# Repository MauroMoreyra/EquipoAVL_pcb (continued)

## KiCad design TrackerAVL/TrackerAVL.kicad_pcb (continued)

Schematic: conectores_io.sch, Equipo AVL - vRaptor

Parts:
D801, D802, D803, D804, D805: PESD5V0L1UA; D_SOD-323_HandSoldering
J801: Conn_02x07_Odd_Even; Molex_Micro-Fit_3.0_43045-1406_2x07-1MP_P3.00mm_Horizontal
J802: Conn_01x15; Molex_Pico_SPOX_87438-0443_1x15
J803: Conn_01x04; Molex_Pico_SPOX_87438-0443_1x04
U801: 74HC4053; TSSOP-16_4.4x5mm_P0.65mm

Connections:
+3V3: J802.1, U801.16; also elsewhere on the board
/AN_IN_0: J801.12; also elsewhere on the board
/AN_IN_1: J801.13; also elsewhere on the board
/AN_IN_2: J801.14; also elsewhere on the board
/CPU/BUZZER: D802.1 (A1), J802.10; also elsewhere on the board
/CPU/DISPLAY_MODE: U801.9, U801.10, U801.11; also elsewhere on the board
/CPU/IBUTTON: D801.1 (A1), J802.15; also elsewhere on the board
/Conectores_IO/DISP_0: D805.1 (A1), J802.7, U801.14
/Conectores_IO/DISP_1: D804.1 (A1), J802.8, U801.15
/Conectores_IO/DISP_2: D803.1 (A1), J802.9, U801.4
/Conectores_IO/DISP_SPI_CS1: U801.3; also elsewhere on the board
/Conectores_IO/PROG_RX: J803.3; also elsewhere on the board
/Conectores_IO/PROG_TX: J803.2; also elsewhere on the board
/DIG_IN_0: J801.3; also elsewhere on the board
/DIG_IN_1: J801.4; also elsewhere on the board
/DIG_IN_2: J801.5; also elsewhere on the board
/DIG_OUT_0: J801.9; also elsewhere on the board
/DIG_OUT_1: J801.10; also elsewhere on the board
/DIG_OUT_2: J801.11; also elsewhere on the board
/I2C_SCL: U801.12; also elsewhere on the board
/I2C_SDA: U801.2; also elsewhere on the board
/IGN: J801.8; also elsewhere on the board
/MIC+: J802.14; also elsewhere on the board
/MIC-: J802.13; also elsewhere on the board
/SPI_MOSI: U801.1; also elsewhere on the board
/SPI_SCK: U801.13; also elsewhere on the board
/SPK+: J802.11; also elsewhere on the board
/SPK-: J802.12; also elsewhere on the board
/TEC_0: J802.3; also elsewhere on the board
/TEC_1: J802.4; also elsewhere on the board
/TEC_2: J802.5; also elsewhere on the board
/TEC_3: J802.6; also elsewhere on the board
/VBAT: J801.1; also elsewhere on the board
GND: D801.2 (A2), D802.2 (A2), D803.2 (A2), D804.2 (A2), D805.2 (A2), J801.2, J801.6, J801.7, J802.2, J803.1, J803.4, U801.6, U801.7, U801.8; also elsewhere on the board

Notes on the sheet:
PWR Display
Teclas consola
Display consola
Audio consola
IButton consola
Entradas digitales
Tensión de batería
Señal de ignición
Salidas digitales
Entradas analógicas
Interfaz principal
Interfaz consola
Interfaz programación
Protecciones IO
Buzzer consola
Lógica de switcheo de buses I2C/SPI (según protocolo del display)
I2C_SCL / SPI_SCK
I2C_SDA / SPI_MOSI
NC / SPI_CS1
DM = 0 / DM = 1

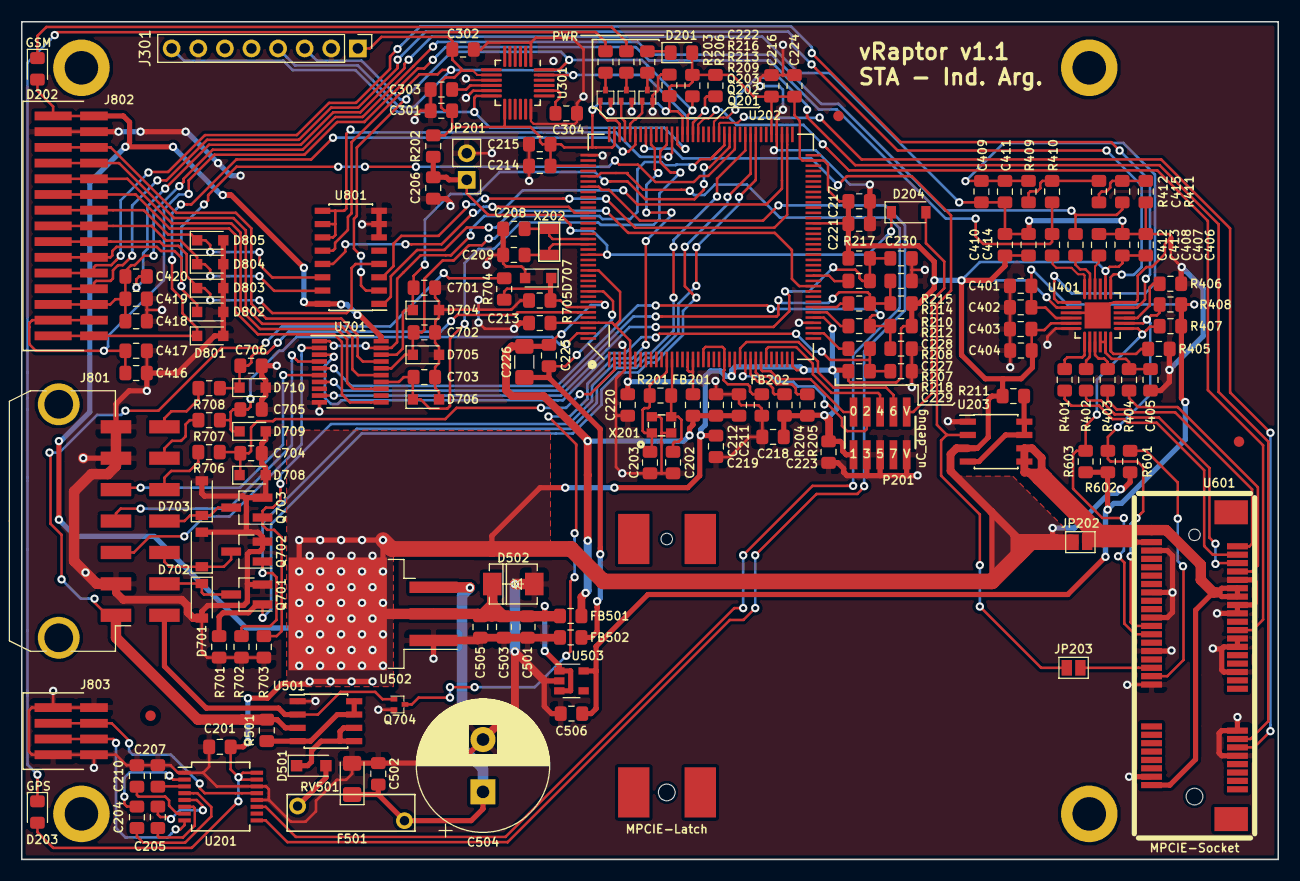
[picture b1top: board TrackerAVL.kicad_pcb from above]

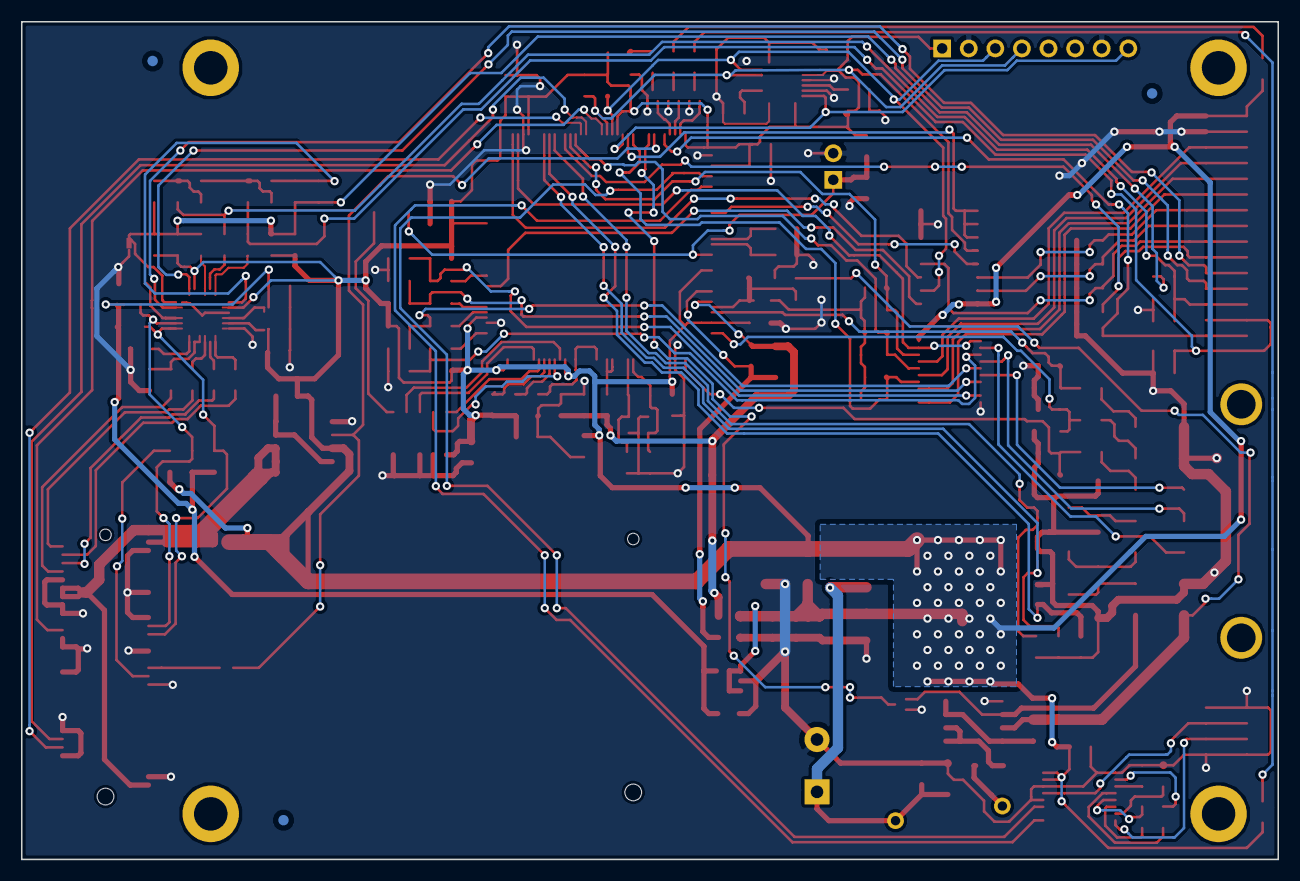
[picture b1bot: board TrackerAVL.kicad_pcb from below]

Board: 2 copper layers, 120.0 x 80.0 mm, 174 parts (3 on the bottom side), 122 nets.

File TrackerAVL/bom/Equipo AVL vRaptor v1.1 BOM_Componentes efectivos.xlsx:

Id | Identificador | Empaquetado | Cantidad | Identificación | Suministrador y ref | S/N | Cantidad real | Componentes Not Mounted | Comentario / Justificación
1 | J301 | PinHeader_1x08_P2.54mm_Vertical | 1 | Conn_01x08 |  | NO | 0
2 | H102,H101,H103,H104 | MountingHole_3.2mm_M3_Pad_Thin | 4 | MountingHole |  | NO | 0
3 | C401,C207,C201,C204,C205,C206,C210,C211,C212,C213,C214,C215,C216,C217,C218,C219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 | C_0805_2012Metric_Pad1.15x1.40mm_HandSolder | 41 | 100nF |  | SI | 38 | C206, C211, C212
4 | C304 | C_0805_2012Metric_Pad1.15x1.40mm_HandSolder | 1 | 2.2nF |  | SI | 1
5 | U401 | NAU8814_QFN-24_4x4mm_Pitch0.5mm_EPAD_HandSoldering | 1 | NAU8814 |  | SI | 1
6 | U301 | InvenSense_QFN-24_4x4mm_P0.5mm_HandSoldering | 1 | MPU-6050 |  | SI | 1
7 | U601 | mpcie-socket-latch | 1 | MPCIE-Socket |  | SI | 1
8 | U202 | LQFP144-M05 | 1 | LPC4337JBD144 |  | SI | 1
9 | U801 | SOIC-16_3.9x9.9mm_P1.27mm | 1 | 74HC4053 |  | SI | 1
10 | X201 | FA238V-XTAL | 1 | 12MHz |  | SI | 1
11 | U501,U203 | SOIC-8_3.9x4.9mm_P1.27mm | 2 | STS8C5H30L |  | SI | 1 | U203
12 | R501,R204,R205,R207,R210,R211,R214,R217,R405,R406,R407,R408,R601,R602,R603,R701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 | R_0805_2012Metric_Pad1.15x1.40mm_HandSolder | 18 | 10K |  | SI | 17 | R211 | R211: por optarse secuencia de reset mediante #PERST
13 | FB502,FB501 | L_0805_2012Metric_Pad1.15x1.40mm_HandSolder | 2 | HZ0805E601R-10 |  | SI | 2
14 | C202,C203,C208,C209,C405 | C_0805_2012Metric_Pad1.15x1.40mm_HandSolder | 5 | 20pF |  | SI | 5
15 | C226 | C_1206_3216Metric_Pad1.42x1.75mm_HandSolder | 1 | 10uF 10V |  | SI | 1
16 | C402,C404,C407,C408,C411,C414,C420 | C_0805_2012Metric_Pad1.15x1.40mm_HandSolder | 7 | 4.7uF |  | SI | 7
17 | C412,C413 | C_0805_2012Metric_Pad1.15x1.40mm_HandSolder | 2 | 1uF |  | SI | 2
18 | C415 | C_0805_2012Metric_Pad1.15x1.40mm_HandSolder | 1 | 10nF |  | SI | 1
19 | C416,C418 | C_0805_2012Metric_Pad1.15x1.40mm_HandSolder | 2 | 10pF |  | SI | 2
20 | C417,C419 | C_0805_2012Metric_Pad1.15x1.40mm_HandSolder | 2 | 33pF |  | SI | 2
21 | C503,C505,C506 | C_0805_2012Metric_Pad1.15x1.40mm_HandSolder | 3 | 4.7uF 6.3V |  | SI | 3
22 | C504 | CP_Radial_D12.5mm_P5.00mm | 1 | 1000uF 50V |  | SI | 1
23 | D201 | LED_0805_2012Metric_Pad1.15x1.40mm_HandSolder | 1 | LED ROJO |  | NO | 0
24 | D202 | LED_0805_2012Metric_Pad1.15x1.40mm_HandSolder | 1 | LED AZUL |  | SI | 1
25 | D203 | LED_0805_2012Metric_Pad1.15x1.40mm_HandSolder | 1 | LED VERDE |  | SI | 1
26 | D204 | D_SOD-123 | 1 | 1N4148 |  | SI | 1
27 | D501 | D_SOD-123F | 1 | PMEG3020EH |  | SI | 1
28 | D502 | DO-214AC (SMA) | 1 | SMAZ5V6 |  | SI | 1
29 | D701,D702,D703 | D_SOD-123 | 3 | BZT52C36 |  | SI | 3
30 | D704,D705,D706,D707,D708,D709,D710,D801,D802,D803,D804,D805 | D_SOD-323_HandSoldering | 12 | PESD5V0L1UA |  | SI | 9 | D704, D705, D706 | D704, D705, D706: por existir protección mediante buffer
31 | F101,F102,F103,F104,F105,F106 | Fiducial_1mm_Dia_2mm_Outer | 6 | Fiducial |  | NO | 0
32 | F501 | 60R300XF | 1 | 60R300XF |  | SI | 1
33 | FB201,FB202 | L_0805_2012Metric_Pad1.15x1.40mm_HandSolder | 2 | MI0805M221R-10 |  | NO | 0 | FB201, FB202 | FB201, FB202: por no utilizarse funcionalidad USB
34 | J801 | Molex_Micro-Fit_3.0_43045-1406_2x07-1MP_P3.00mm_Horizontal | 1 | Conn_02x07_Odd_Even |  | SI | 1
35 | J802 | Molex_Pico_SPOX_87438-0443_1x15 | 1 | Conn_01x15 |  | SI | 1
36 | J803 | Molex_Pico_SPOX_87438-0443_1x04 | 1 | Conn_01x04 |  | SI | 1
37 | JP201 | PinHeader_1x02_P2.54mm_Vertical | 1 | JP |  | NO | 0
38 | JP202,JP203 | SolderJumper-2_P1.3mm_Open_Pad1.0x1.5mm | 2 | SolderJumper_2_Open |  | NO | 0
39 | P201 | Pin_Array_5x2_1.27mm_SMD | 1 | uC_debug |  | SI | 1
40 | Q201,Q202,Q203,Q704 | SOT-523_(SOT-416) | 4 | DTC043ZEBTL |  | SI | 3 | Q201 | Q201: por no utilizarse Led Rojo
41 | Q701,Q702,Q703 | SOT-23_Handsoldering | 3 | 2N7002P |  | SI | 3
42 | R201 | R_0805_2012Metric_Pad1.15x1.40mm_HandSolder | 1 | 10M |  | SI | 1
43 | R202 | R_0805_2012Metric_Pad1.15x1.40mm_HandSolder | 1 | 100K |  | SI | 1
44 | R203,R206 | R_0805_2012Metric_Pad1.15x1.40mm_HandSolder | 2 | 2K2 |  | SI | 2
45 | R208,R212,R215,R218,R409,R412 | R_0805_2012Metric_Pad1.15x1.40mm_HandSolder | 6 | 1K |  | SI | 6
46 | R209,R213,R216 | R_0805_2012Metric_Pad1.15x1.40mm_HandSolder | 3 | 680 |  | SI | 2 | R209 | R209: por no utilizarse Led Rojo
47 | R401,R402,R403,R404 | R_0805_2012Metric_Pad1.15x1.40mm_HandSolder | 4 | 22R |  | SI | 4
48 | R410,R411,R706,R707,R708 | R_0805_2012Metric_Pad1.15x1.40mm_HandSolder | 5 | 1K2 |  | SI | 5
49 | R704 | R_0805_2012Metric_Pad1.15x1.40mm_HandSolder | 1 | 10K 1% |  | SI | 1
50 | R705 | R_0805_2012Metric_Pad1.15x1.40mm_HandSolder | 1 | 1210 1% |  | SI | 1
51 | RV501 | D_1206_3216Metric_Pad1.42x1.75mm_HandSolder | 1 | 30VDC |  | SI | 1
52 | U201 | SSOP-16_5.3x6.2mm_P0.65mm | 1 | MAX3221 |  | SI | 1
53 | U502 | TO-263-3_TabPin2 | 1 | LD1085D2T33R |  | SI | 1
54 | U503 | TSOP-5_NCP114 | 1 | NCP114ASN180T1G |  | SI | 1
55 | U701 | TSSOP-20_4.4x6.5mm_P0.65mm | 1 | 74LVC244APW |  | SI | 1
56 | X202 | 32.768-XTAL-SMD | 1 | 32.768K |  | SI | 1
57 | JP401 | NetTie-2_SMD_Pad0.5mm | 1 | Jumper |  | NO | 0

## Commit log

2018-09-25 Agrego archivos. Trabajando en esquemático.
2018-09-25 Cambios en sch
2018-10-13 Cambios en sch y adición de documentación
2018-10-18 Cambios en sch y add docs
2018-10-30 EquipoAVL-vRaptor1.0 sch-finalizado
2018-10-30 Cambios en pcb
2018-11-02 Esquemático: se corrige símbolo FILTROS
2018-11-05 Cambios en pcb y modelos 3d
2018-11-07 PCB terminado, pendiente revisión
2018-11-08 vRaptor-v1.1-init
2018-11-08 Se modifica huella NAU8814 a QFN-24_HandSoldering
    Falta modificar resto de huellas
2018-11-08 Se modifica huella NAU8814 a QFN-24_HandSoldering
2018-11-10 Se modifica huella MPU6050 a QFN-24_HandSoldering
    Pendiente hacer cambios de pistas según recomendaciones que figuran en el diseño del pcb.
2018-11-13 Se archivan huellas en libreria del proyecto
2018-11-13 Últimos cambios en pcb
2018-11-13 Cambios menores en archivos
2018-11-13 Pendiente revisión PCB y esquemático
2018-11-13 Modificaciones varias
    Se modifica acceso de pistas a pads (ahora a 90°).
    Se agregan archivos de información al proyecto.
    Se corrigen elementos 3d 24-QFN.
    Modificaciones varias de pistas.
2018-11-14 Cambio de nombre de archivo
2018-11-14 modificaciones en pcb
2018-11-14 PCB terminado, para su revisión final
2018-11-15 Cambios en README, ahora incluye información de versiones
2018-11-15 Generación de archivos gerber, drills, bom
2018-11-15 Preparación de gerbers para enviar a fabricante Elecrow
2018-11-18 Actualización modelos 3d
2018-11-28 Add doc revisión profesor
2018-11-29 Update files
2018-11-30 Update BOM files and README
2018-11-30 Update 3D Models
2018-11-30 Starting vRaptor v1.2 at release
